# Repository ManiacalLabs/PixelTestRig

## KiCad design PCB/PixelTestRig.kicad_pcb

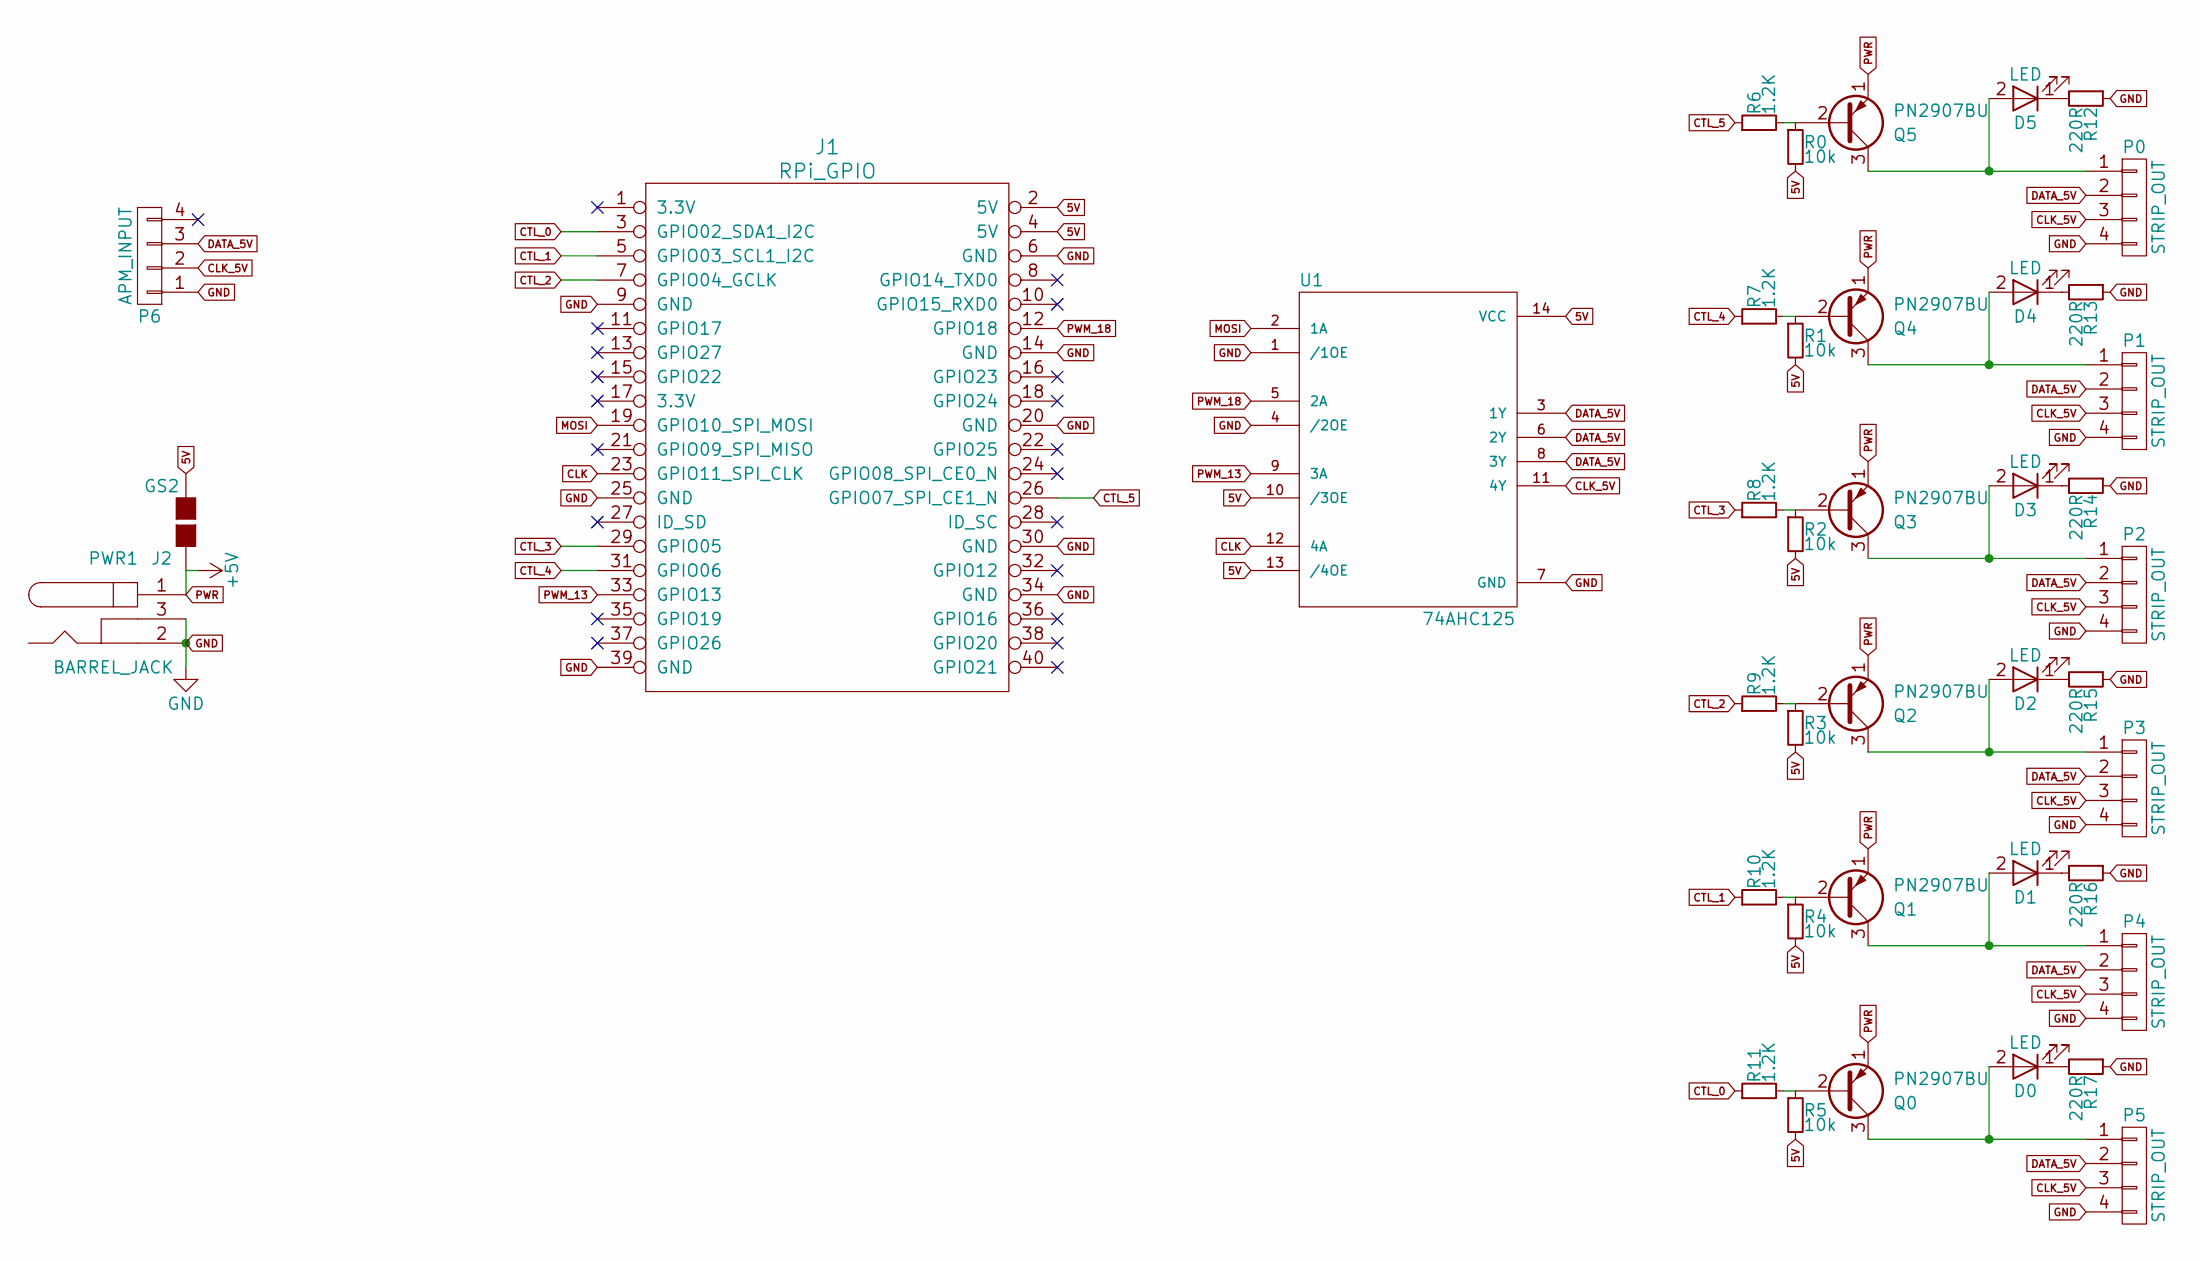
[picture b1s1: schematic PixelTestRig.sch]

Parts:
D0, D1, D2, D3, D4, D5: LED; LED_D3.0mm
J1: RPi_GPIO; Pin_Header_Straight_2x20
J2: GS2
P0, P1, P2, P3, P4, P5: STRIP_OUT; mpt_0,5%2f4-2,54
P6: APM_INPUT; mpt_0,5%2f4-2,54
PWR1: BARREL_JACK; ML_BARREL_JACK_ROUND_PADS_SHORT
Q0, Q1, Q2, Q3, Q4, Q5: PN2907BU; TO-92_Inline_Narrow_Oval
R0, R1, R2, R3, R4, R5: 10k; R_Axial_DIN0204_L3.6mm_D1.6mm_P5.08mm_Horizontal
R6, R7, R8, R9, R10, R11: 1.2K; R_Axial_DIN0204_L3.6mm_D1.6mm_P5.08mm_Horizontal
R12, R13, R14, R15, R16, R17: 220R; R_Axial_DIN0204_L3.6mm_D1.6mm_P5.08mm_Horizontal
U1: 74AHC125; DIP-14_W7.62mm_LongPads

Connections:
5V: J1.2 (5V), J1.4 (5V), J2.2 (G2), R0.2, R1.2, R2.2, R3.2, R4.2, R5.2, U1.10 (/3OE), U1.13 (/4OE), U1.14 (VCC)
CLK: J1.23 (GPIO11_SPI_CLK), U1.12 (4A)
CLK_5V: P0.3, P1.3, P2.3, P3.3, P4.3, P5.3, P6.2, U1.11 (4Y)
CTL_0: J1.3 (GPIO02_SDA1_I2C), R11.1
CTL_1: J1.5 (GPIO03_SCL1_I2C), R10.1
CTL_2: J1.7 (GPIO04_GCLK), R9.1
CTL_3: J1.29 (GPIO05), R8.1
CTL_4: J1.31 (GPIO06), R7.1
CTL_5: J1.26 (GPIO07_SPI_CE1_N), R6.1
DATA_5V: P0.2, P1.2, P2.2, P3.2, P4.2, P5.2, P6.3, U1.3 (1Y), U1.6 (2Y), U1.8 (3Y)
GND: J1.6 (GND), J1.9 (GND), J1.14 (GND), J1.20 (GND), J1.25 (GND), J1.30 (GND), J1.34 (GND), J1.39 (GND), P0.4, P1.4, P2.4, P3.4, P4.4, P5.4, P6.1, PWR1.2, PWR1.3, R12.1, R13.1, R14.1, R15.1, R16.1, R17.1, U1.1 (/1OE), U1.4 (/2OE), U1.7 (GND)
MOSI: J1.19 (GPIO10_SPI_MOSI), U1.2 (1A)
unnamed: D0.1 (K), R17.2
unnamed: D0.2 (A), P5.1, Q0.3 (C)
unnamed: D1.1 (K), R16.2
unnamed: D1.2 (A), P4.1, Q1.3 (C)
unnamed: D2.1 (K), R15.2
unnamed: D2.2 (A), P3.1, Q2.3 (C)
unnamed: D3.1 (K), R14.2
unnamed: D3.2 (A), P2.1, Q3.3 (C)
unnamed: D4.1 (K), R13.2
unnamed: D4.2 (A), P1.1, Q4.3 (C)
unnamed: D5.1 (K), R12.2
unnamed: D5.2 (A), P0.1, Q5.3 (C)
unnamed: Q0.2 (B), R5.1, R11.2
unnamed: Q1.2 (B), R4.1, R10.2
unnamed: Q2.2 (B), R3.1, R9.2
unnamed: Q3.2 (B), R2.1, R8.2
unnamed: Q4.2 (B), R1.1, R7.2
unnamed: Q5.2 (B), R0.1, R6.2
PWM_13: J1.33 (GPIO13), U1.9 (3A)
PWM_18: J1.12 (GPIO18), U1.5 (2A)
PWR: J2.1 (G1), PWR1.1, Q0.1 (E), Q1.1 (E), Q2.1 (E), Q3.1 (E), Q4.1 (E), Q5.1 (E)

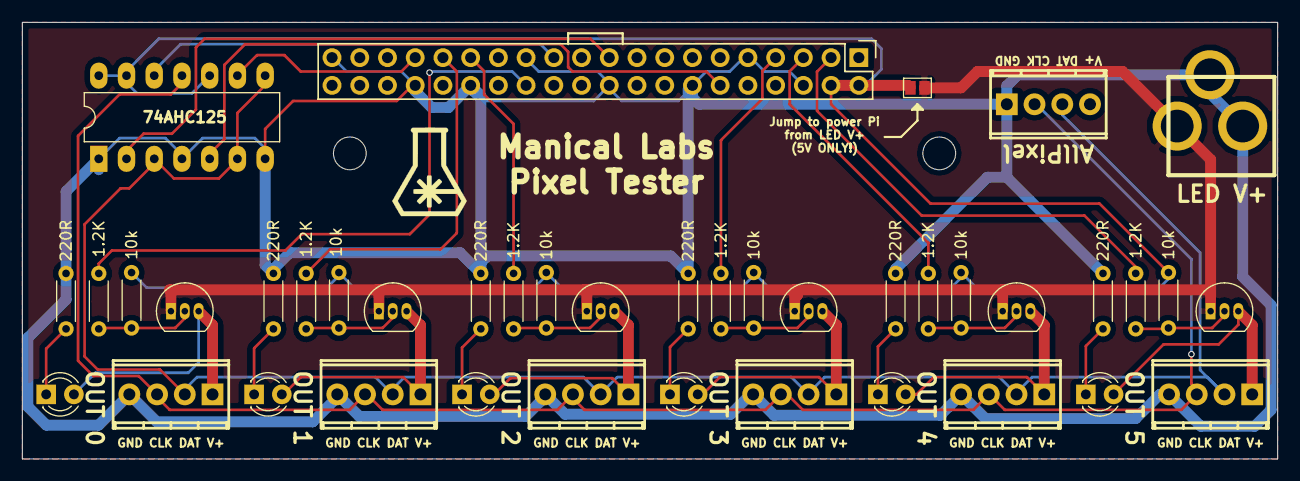
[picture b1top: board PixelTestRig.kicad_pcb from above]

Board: 2 copper layers, 115.0 x 40.0 mm, 41 parts (0 on the bottom side), 33 nets.

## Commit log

2018-01-12 Rough schematic
2018-01-13 Completed layout
2018-01-14 minor updates
2018-01-15 Now using PNP transistor
2018-01-15 Updated CvPcb
2018-01-15 layout redone with PNP
